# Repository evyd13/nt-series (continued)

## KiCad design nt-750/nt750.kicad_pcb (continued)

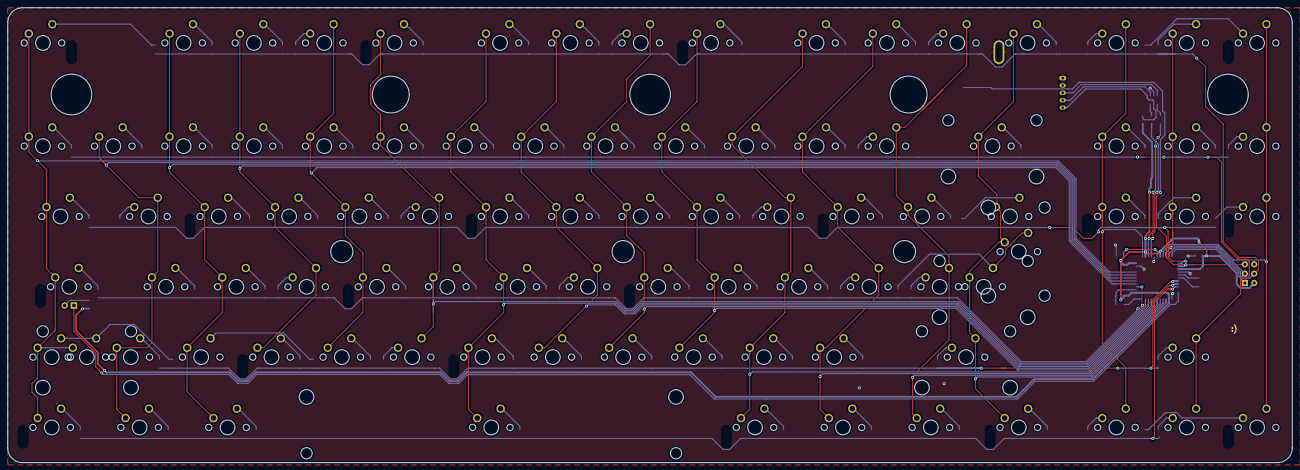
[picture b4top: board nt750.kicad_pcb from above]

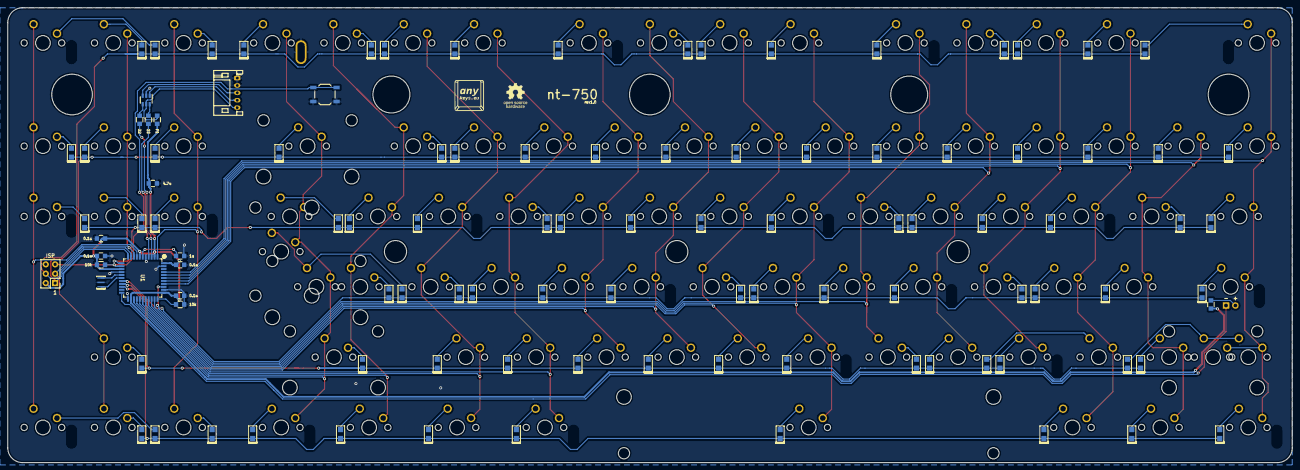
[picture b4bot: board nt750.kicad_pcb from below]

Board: 2 copper layers, 347.9 x 123.2 mm, 199 parts (107 on the bottom side), 128 nets.

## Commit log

2020-10-06 Upload PCB files
2020-10-06 Add readme's
2020-10-25 nt-660 rev1.1
2020-10-25 Add PCB images
2020-10-25 fix images
2020-12-19 Update PCB footprints/gerbers
2021-03-21 Add nt660 plate file
2021-08-18 Create README.md
    Plate Readme
2021-08-18 Add files via upload
    Plate files for fc980m
2021-12-08 Add files via upload
    V6 is reversible
2022-01-03 Plate Files for FC980m/nt-980 PCBs
2022-02-01 Upload nt210 files
2022-06-24 add nt-650
2022-06-24 Remove sub-gitignores
2022-07-07 Add nt-10
